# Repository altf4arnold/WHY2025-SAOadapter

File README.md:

# WHY2025 badge SAO adapter

Readme coming later, enjoy the camp!

# Pictures :

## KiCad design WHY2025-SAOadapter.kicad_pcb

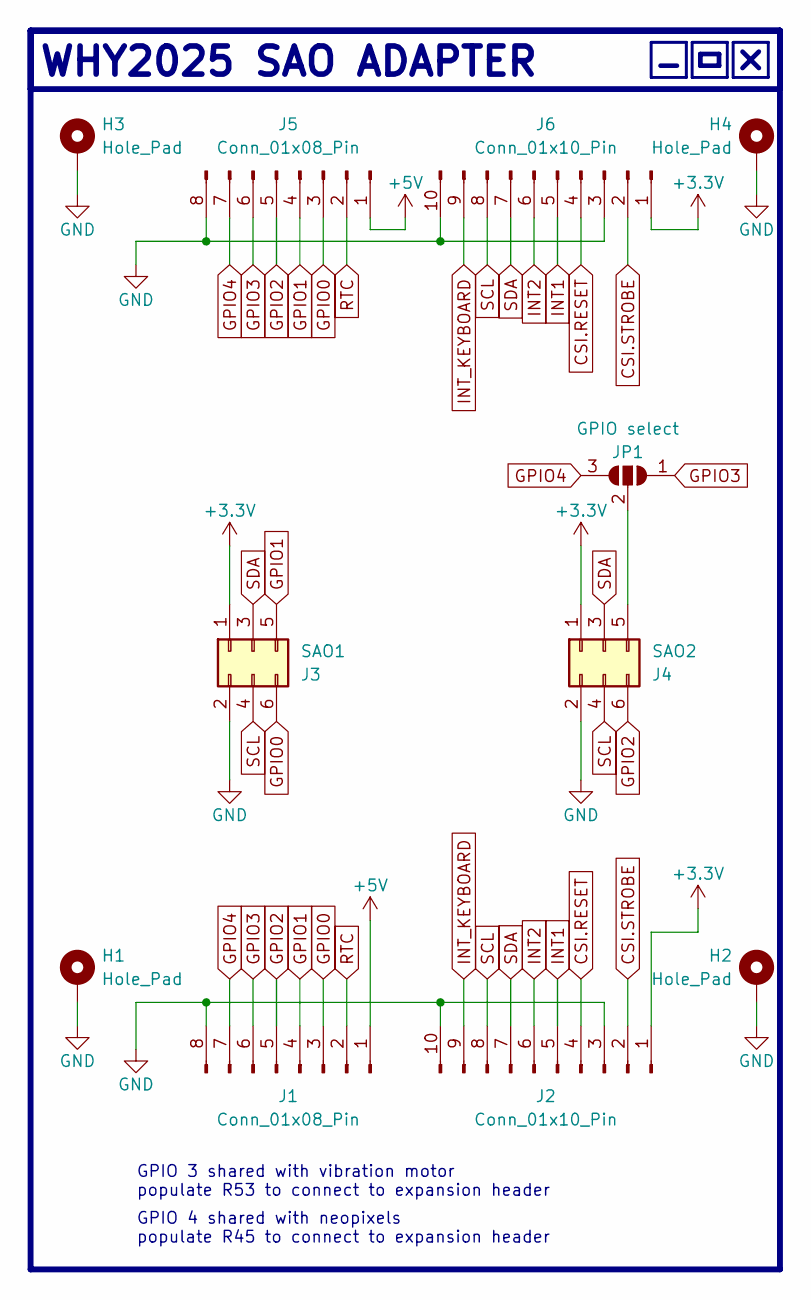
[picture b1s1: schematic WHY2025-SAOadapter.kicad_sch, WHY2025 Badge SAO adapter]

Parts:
H1, H2, H3, H4: Hole_Pad; MountingHole_2.2mm_M2_Pad
J1: Conn_01x08_Pin; PinHeader_1x08_P2.54mm_Horizontal
J2: Conn_01x10_Pin; PinHeader_1x10_P2.54mm_Horizontal
J3: SAO1; PinSocket_2x03_P2.54mm_Vertical
J4: SAO2; PinSocket_2x03_P2.54mm_Vertical
J5: Conn_01x08_Pin; PinSocket_1x08_P2.54mm_Horizontal
J6: Conn_01x10_Pin; PinSocket_1x10_P2.54mm_Horizontal
JP1: GPIO select; SolderJumper-3_P1.3mm_Open_RoundedPad1.0x1.5mm

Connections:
+3.3V: J2.1, J3.1, J4.1, J6.1
+5V: J1.1, J5.1
CSI.RESET: J2.4, J6.4
CSI.STROBE: J2.2, J6.2
GND: H1.1, H2.1, H3.1, H4.1, J1.8, J2.3, J2.10, J3.2, J4.2, J5.8, J6.3, J6.10
GPIO0: J1.3, J3.6, J5.3
GPIO1: J1.4, J3.5, J5.4
GPIO2: J1.5, J4.6, J5.5
GPIO3: J1.6, J5.6, JP1.1 (A)
GPIO4: J1.7, J5.7, JP1.3 (B)
INT1: J2.5, J6.5
INT2: J2.6, J6.6
INT_KEYBOARD: J2.9, J6.9
unnamed: J4.5, JP1.2 (C)
RTC: J1.2, J5.2
SCL: J2.8, J3.4, J4.4, J6.8
SDA: J2.7, J3.3, J4.3, J6.7

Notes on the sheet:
WHY2025 SAO ADAPTER
GPIO 4 shared with neopixels populate R45 to connect to expansion header
GPIO 3 shared with vibration motor populate R53 to connect to expansion header

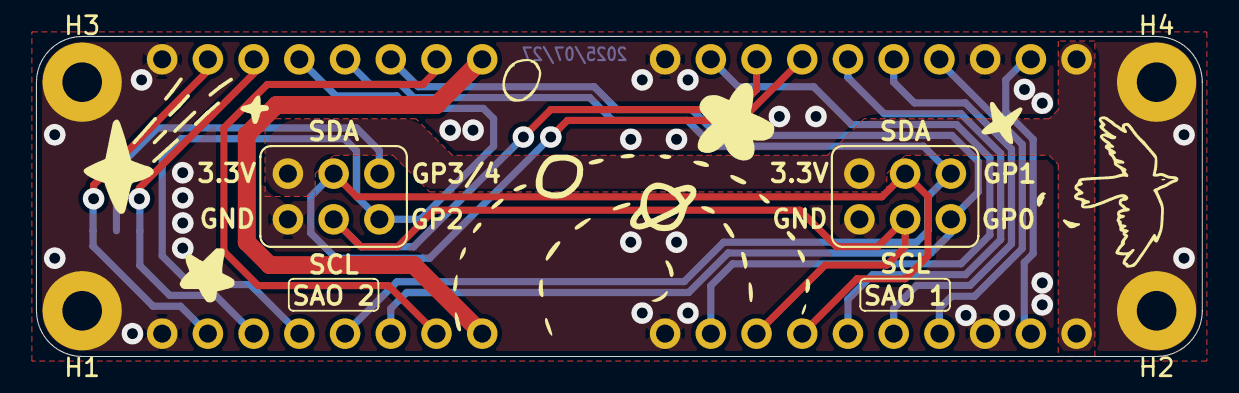
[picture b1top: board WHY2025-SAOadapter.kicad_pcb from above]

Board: 2 copper layers, 64.8 x 17.8 mm, 11 parts (1 on the bottom side), 17 nets.

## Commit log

2025-08-10 added gitignore and removed backups
2025-08-11 temp updated readme
2025-08-11 removed useless file
2025-12-28 Adding pictures
